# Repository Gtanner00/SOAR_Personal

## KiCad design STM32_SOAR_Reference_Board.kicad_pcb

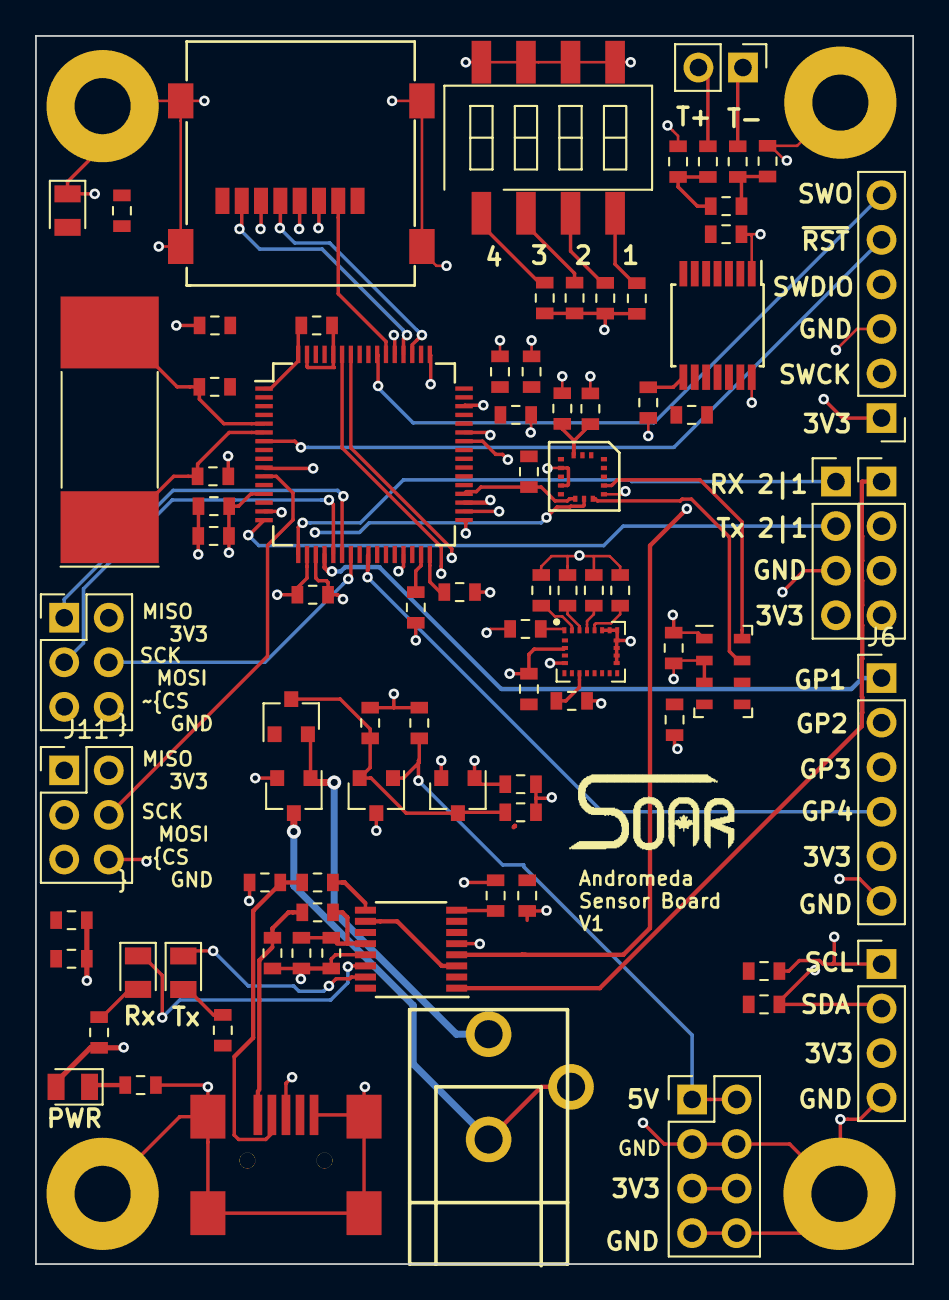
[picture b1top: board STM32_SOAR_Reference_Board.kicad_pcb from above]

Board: 4 copper layers, 50.0 x 70.0 mm, 89 parts (0 on the bottom side), 68 nets.

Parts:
C1, C2: 47pF; C_0603_1608Metric
C3, C19, C23, C24: 10nF; C_0603_1608Metric
C4: 4.7uF; C_0603_1608Metric
C5, C15, C16, C18, C20, C22, C29, C30, C31, C32: 100nF; C_0603_1608Metric
C6, C17: 1uF; C_0603_1608Metric
C7, C9: 0.22uF; C_0603_1608Metric
C8, C10, C11: 2.2uF; C_0603_1608Metric
C12, C14: 24pF; C_0603_1608Metric
C13, C21, C28, C33: 10uF; C_0603_1608Metric
C25, C26, C27: 0.1uF; C_0603_1608Metric
D1, D4: Green; LED_0805_2012Metric
D2: Red; LED_0805_2012Metric
D3: D_Schottky_x2_KCom_AAK; SOT-23
D5: LED; LED_0805_2012Metric
J1: USB_MINIB; USB-Mini-B
J2: Barrel_Jack; CUI_PJ-102A
J3: Conn_02x04_Odd_Even; PinHeader_2x04_P2.54mm_Vertical
J4: Micro_SD_Card; Conn,Molex,Hinged_microSD
J5: Conn_01x02; PinHeader_1x02_P2.54mm_Vertical
J6, J7: Conn_01x06; PinHeader_1x06_P2.54mm_Vertical
J8, J9, J13: Conn_01x04; PinHeader_1x04_P2.54mm_Vertical
J11, J12: Conn_02x03_Odd_Even; PinHeader_2x03_P2.54mm_Vertical
L1: Ferrite_Bead; L_0603_1608Metric
LOGO_SOAR: LOGO_SOAR
MK1, MK2, MK3, MK4: Mounting_Hole_PAD; MountingHole_3.2mm_M3_Pad
Q1: Q_NMOS_GSD; SOT-23
R1, R2: 27; R_0603_1608Metric
R3, R4, R5, R20: 330; R_0603_1608Metric
R6, R7, R8, R9, R12, R13, R14, R15, R16, R17, R18, R19, R21, R22: 10K; R_0603_1608Metric
R10, R11: 100; R_0603_1608Metric
SW1: SW_DIP_x04; SW_DIP_x4_W8.61mm_Slide_LowProfile
U1: FT230XS; SSOP-16_3.9x4.9mm_P0.635mm
U2: AP2210-3.3; SOT-23
U3: LM3480-5.0; SOT-23
U4: STM32F405R; LQFP-64_10x10mm_P0.5mm
U5: LIS3DH; LGA-16
U6: MAX31856; TSSOP-14_4.4x5mm_P0.65mm
U7: LSM9DS1; LGA-24L_3x3.5mm_P0.43mm
U8: MS5607; LGA-8_3x5mm_P1.25mm
Y1: Crystal_8MHz_18pf; Crystal_SMD_SeikoEpson_MA505-2Pin_12.7x5.1mm

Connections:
+3V3: C8.1, C13.1, C15.1, C16.1, C17.1, C18.1, C19.1, C20.1, C21.1, C22.1, C26.1, C27.1, C30.1, C31.1, C32.1, C33.1, D4.2, J3.5, J3.6, J4.4, J6.5, J7.1, J8.4, J9.4, J11.2, J12.2, J13.3, R3.1, R4.2, R6.1, R7.1, R8.1, R9.1, R12.1, R13.1, R14.1, R15.1, R16.1, R17.1, R18.1, R19.1, R21.1, R22.1, U2.1, U4.1, U4.13, U4.19, U4.32, U4.48, U4.64, U5.1, U5.14, U6.5, U6.8, U7.1, U7.3, U7.22, U7.23, U8.1
+5V: C9.1, J3.1, J3.2, U3.1
/Power and FTDI/RX_LED: D2.1, U1.14
/Power and FTDI/TX_LED: D1.1, U1.15
A/G_INT: U4.27, U7.11
A/G_~CS: R13.2, U4.30, U7.7
A_INT: U4.38, U5.11
Accel_~CS: R8.2, U4.36, U5.8
Baro_~CS: R14.2, U4.24, U8.4, U8.5
GND: C1.2, C2.2, C3.2, C4.2, C5.2, C6.2, C7.2, C8.2, C9.2, C10.2, C11.2, C12.2, C13.2, C14.2, C15.2, C16.2, C17.2, C18.2, C19.2, C20.2, C21.2, C22.2, C23.2, C24.1, C26.2, C27.2, C28.2, C29.2, C30.2, C31.2, C32.2, C33.2, D5.1, J1.5, J1.6, J3.3, J3.4, J3.7, J3.8, J4.6, J6.6, J7.3, J8.3, J9.3, J11.6, J12.6, J13.4, MK1.1, MK2.1, MK3.1, MK4.1, Q1.2, R5.2, SW1.5, SW1.6, SW1.7, SW1.8, U1.5, U1.13, U2.2, U3.3, U4.12, U4.18, U4.60, U4.63, U5.5, U5.10, U5.12, U6.1, U6.14, U7.14, U7.15, U7.16, U7.17, U7.18, U7.19, U7.20, U8.2, U8.3
GPIO1: J6.1, U4.20
GPIO2: J6.2, U4.35
GPIO3: J6.3, U4.34
GPIO4: J6.4, U4.25
GPIO6: R20.1, U4.2
GPIO7: R19.2, SW1.1, U4.41
GPIO8: R18.2, SW1.2, U4.40
GPIO9: R17.2, SW1.3, U4.39
GPIO10: R16.2, SW1.4, U4.37
I2C1_SCL: J13.1, R6.2, U4.58
I2C1_SDA: J13.2, R7.2, U4.59
MAG_INT: U4.26, U7.10
MAG_~CS: R15.2, U4.28, U7.8
NRST: J7.5, U4.7
unnamed: C1.1, J1.2, R1.2
unnamed: C2.1, J1.3, R2.2
unnamed: C3.1, J1.1, L1.2
unnamed: C10.1, U4.47
unnamed: C11.1, U4.31
unnamed: C12.1, U4.6, Y1.1
unnamed: C14.1, U4.5, Y1.2
unnamed: C23.1, C25.2, R11.1, U6.3
unnamed: C24.2, C25.1, R10.1, U6.4
unnamed: C28.1, U7.21
unnamed: C29.1, U7.24
unnamed: D1.2, R3.2
unnamed: D2.2, R4.1
unnamed: D4.1, R5.1
unnamed: D5.2, R20.2
unnamed: J2.2, J2.3, Q1.3
unnamed: J5.1, R11.2, U6.2
unnamed: J5.2, R10.2
unnamed: R1.1, U1.9
unnamed: R2.1, U1.8
unnamed: U1.3, U1.10
SD_SPI_MISO: J4.7, U4.52
SD_SPI_MOSI: J4.3, U4.53
SD_SPI_SCK: J4.5, U4.51
SD_~CS: J4.2, R9.2, U4.54
SPI1_MISO: J12.1, U4.22, U6.11, U7.5, U7.6
SPI1_MOSI: J12.4, U4.23, U6.12, U7.4
SPI1_SCK: J12.3, U4.21, U6.10, U7.2
SPI1_~CS: J12.5, R22.2, U4.15
SPI2_MISO: J11.1, U4.10, U5.7, U8.6
SPI2_MOSI: J11.4, U4.11, U5.6, U8.7
SPI2_SCK: J11.3, U4.29, U5.4, U8.8
SPI2_~CS: J11.5, R21.2, U4.33
SWCLK: J7.2, U4.49
SWDIO: J7.4, U4.46
SWO: J7.6, U4.55
Therm_~CS: R12.2, U4.44, U6.9
UART1_RX: J9.1, U1.1, U4.43
UART1_TX: J9.2, U1.4, U4.42
UART2_RX: J8.1, U4.17
UART2_TX: J8.2, U4.16
VBUS: C4.1, C5.1, D3.1, L1.1, U1.12
VDC: C6.1, C7.1, D3.3, U2.3, U3.2
VEXT: D3.2, J2.1, Q1.1

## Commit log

2017-10-22 Initial Commit or schematic and parts directory
2017-12-09 Completed schematic, Digikey parts added. 4 layer routing started.
